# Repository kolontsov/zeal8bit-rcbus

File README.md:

## Zeal 8-bit to RCBus adapter

This is a simple adapter enabling the use of RC2014 and [RCBus](https://smallcomputercentral.com/rcbus/) boards with the [Zeal 8-bit computer](https://zeal8bit.com/) [external port](https://zeal8bit.com/docs/ext_port/) or [backplane](https://www.tindie.com/products/zeal8bit/backplane-pcb-for-zeal-8-bit-computer-4-slots/), with optional port mapping.

Port mapping is important because many RCBus boards use ports larger than 0x80, which is [reserved I/O space](https://zeal8bit.com/docs/memorymap/#io-mapping) on the Zeal 8-bit computer.

To make the board compatible with Zeal 8-bit, any of the A7-A4 address lines can be **inverted** -- see [online configuration tool](https://kolontsov.github.io/zeal8bit-rcbus/).

Tested with:
- [SC729 – RCBus Compact Flash Module](https://smallcomputercentral.com/rcbus/sc700-series/sc729-rcbus-compact-flash-module/) (with [Zeal 8-bit OS](https://github.com/Zeal8bit/Zeal-8-bit-OS))
- [SC725 – RCBus Serial and Timer Module](https://smallcomputercentral.com/rcbus/sc700-series/sc725-rcbus-serial-and-timer-module/) (with RomWBW)
- [16C2552 dual UART for RC2014](https://hackaday.io/project/170819-16c2552-dual-uart-for-rc2014) (with RomWBW)
- (to be added)

No guarantee that it will work with other RCBus boards, but it should be compatible with most of them.

### Bill of Materials

Reference | Description                                    | Comment
--------- | ---------------------------------------------- | --------------------------------------
J1        | 2x25 pin header, 2.54 mm, right angle          | Plugs into Zeal 8-bit backplane
J2        | 2x40 *or* 1x40 pin socket, 2.54mm, right angle | Socket for RCBus board to plug into
JP1, JP2, JP3, JP4 | 2-pin header                          | A7-A4 invert jumpers
U1        | 74HCT86 (DIP-14), with optional socket         | Quad 2-input XOR gate
C1        | 0.1µF ceramic capacitor                        |
JP5       | 2-pin header, 2.54mm                           | (optional) Disable Zeal 8-bit on-board ROM
J3        | 2-pin header, 2.54mm                           | (optional) RX/TX pins of RCBus

### PCB

- Gerber files are in [production](production/) directory (JLCPCB, PCBWay, etc.)
- Read-to-order PCB at [PCBWay](https://www.pcbway.com/project/shareproject/Zeal_8_bit_to_RCBus_adapter_069f3f1e.html)
- Schematics in PDF format: [zeal8bit-rcbus.pdf](docs/zeal8bit-rcbus.pdf)
- KiCad 9.0 project in this directory

### Assembly

In most cases, using a 40-pin socket for connecting RCBus boards is sufficient and easier to use than an 80-pin socket, especially if you need to connect and disconnect frequently.

An 80-pin socket is only required if your RCBus board actually uses the NMI, WAIT, BUSRQ, BUSACK, HALT or A16..A21 lines.

### Configuration

Use the [online configuration tool](https://kolontsov.github.io/zeal8bit-rcbus/) to determine which address lines (A7-A4) need inversion for your specific RCBus board. Set jumpers JP1-JP4 accordingly.

### License

Licensed under [CERN-OHL-P v2](LICENSE).

All trademarks are the property of their respective owners, use of these names does not imply endorsement.

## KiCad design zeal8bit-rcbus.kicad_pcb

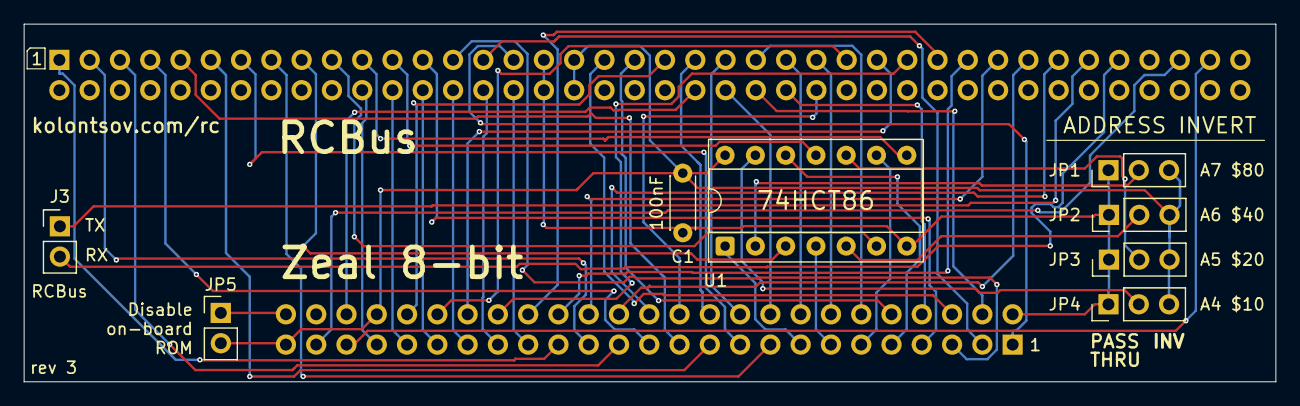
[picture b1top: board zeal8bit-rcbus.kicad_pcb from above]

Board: 2 copper layers, 105.0 x 30.0 mm, 10 parts (0 on the bottom side), 58 nets.

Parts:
C1: 100nF; C_Disc_D4.3mm_W1.9mm_P5.00mm
J1: Zeal 8-bit Extension Port; PinHeader_2x25_P2.54mm_Horizontal
J2: RCBus; PinSocket_2x40_P2.54mm_Horizontal
J3: TX/RX; PinHeader_1x02_P2.54mm_Vertical
JP1: A7 $80; PinHeader_1x03_P2.54mm_Vertical
JP2: A6 $40; PinHeader_1x03_P2.54mm_Vertical
JP3: A5 $20; PinHeader_1x03_P2.54mm_Vertical
JP4: A4 $10; PinHeader_1x03_P2.54mm_Vertical
JP5: ROM; PinHeader_1x02_P2.54mm_Vertical
U1: 74HCT86; DIP-14_W7.62mm_Socket

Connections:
/A0: J1.1, J2.16
/A1: J1.2, J2.15
/A2: J1.3, J2.14
/A3: J1.4, J2.13
/A4_RCBUS: J2.12, U1.11
/A4_ZEAL: J1.5, U1.12
/A5_RCBUS: J2.11, U1.8
/A5_ZEAL: J1.6, U1.9
/A6_RCBUS: J2.10, U1.6
/A6_ZEAL: J1.7, U1.4
/A7_RCBUS: J2.9, U1.3
/A7_ZEAL: J1.8, U1.1
/A8: J1.9, J2.8
/A9: J1.10, J2.7
/A10: J1.11, J2.6
/A11: J1.12, J2.5
/A12: J1.13, J2.4
/A13: J1.14, J2.3
/A14: J1.15, J2.2
/A15: J1.16, J2.1
/A16: J1.17, J2.56
/A17: J1.18, J2.55
/A18: J1.19, J2.54
/A19: J1.20, J2.53
/A20: J1.21, J2.52
/A21: J1.22, J2.51
/CLK: J1.46, J2.21
/D0: J1.45, J2.27
/D1: J1.44, J2.28
/D2: J1.43, J2.29
/D3: J1.42, J2.30
/D4: J1.41, J2.31
/D5: J1.40, J2.32
/D6: J1.39, J2.33
/D7: J1.38, J2.34
/DISABLE_ROM: J1.50, JP5.1 (A)
/IEI: J1.24, J2.38
/IEO: J1.23, J2.39
/RX: J2.36, J3.2
/TX: J2.35, J3.1
/~BUSACK: J1.48, J2.62
/~BUSRQ: J1.27, J2.64
/~HALT: J1.34, J2.63
/~INT: J1.36, J2.22
/~IORQ: J1.32, J2.26
/~M1: J1.28, J2.19
/~MREQ: J1.35, J2.23
/~NMI: J1.37, J2.66
/~RD: J1.33, J2.25
/~RESET: J1.30, J2.20
/~WAIT: J1.29, J2.65
/~WR: J1.31, J2.24
GND: C1.2, J1.26, J2.17, J2.57, JP1.1 (A), JP2.1 (A), JP3.1 (A), JP4.1 (A), U1.7 (GND)
unnamed: JP1.2 (C), U1.2
unnamed: JP2.2 (C), U1.5
unnamed: JP3.2 (C), U1.10
unnamed: JP4.2 (C), U1.13
VCC: C1.1, J1.25, J1.47, J2.18, J2.58, JP1.3 (B), JP2.3 (B), JP3.3 (B), JP4.3 (B), JP5.2 (B), U1.14 (VCC)

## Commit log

2025-08-09 initial revision
2025-08-09 add link to PCBWay project
